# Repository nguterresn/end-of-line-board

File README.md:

## End Of Line Board for Testing

### Quick Introduction

Normally, in the world of _access control_, a [contact sensor](https://www.gensecurity.com/blog/how-do-contatct-sensors-work) is either open or closed. This is essentially true if the system does not support **end of line**.
End of line increases the number of avaialble _states_ of a contact sensor, from two to four:

| Opened | Closed | (new) Shorted | (new) Cut |
|--------|--------|---------|-----|

This is very important in Alarm and Fire systems, where these four states are essential.

### Board

This design aims to test all the possible configurations for end of line: 

|             | **Single Resistor Line Shorted** | **Single Resistor Line Cut** | **Double Resistor** |
|-------------|:--------------------------------:|:----------------------------:|:-------------------:|
| **Opened**  |                 ✅               |               ✅              |          ✅          |
| **Closed**  |                 ✅                |               ✅              |          ✅          |
| **Shorted** |                 ✅                |               ❌              |          ✅          |
| **Cut**     |                 ❌                |               ✅              |          ✅          |

There a is good [document here](https://github.com/nguterresn/end-of-line-board/blob/master/docs/EOL-Types.pdf) explaining the difference between configurations.

### 3D View

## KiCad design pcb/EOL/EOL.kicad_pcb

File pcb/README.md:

## Description
##### This is where the pcb files are. Normally, here is where a KiCad project is created. 

## Directory Structure

- **pcb**
    - bom
    - gerber
    - svg
    - ... (some package folders)

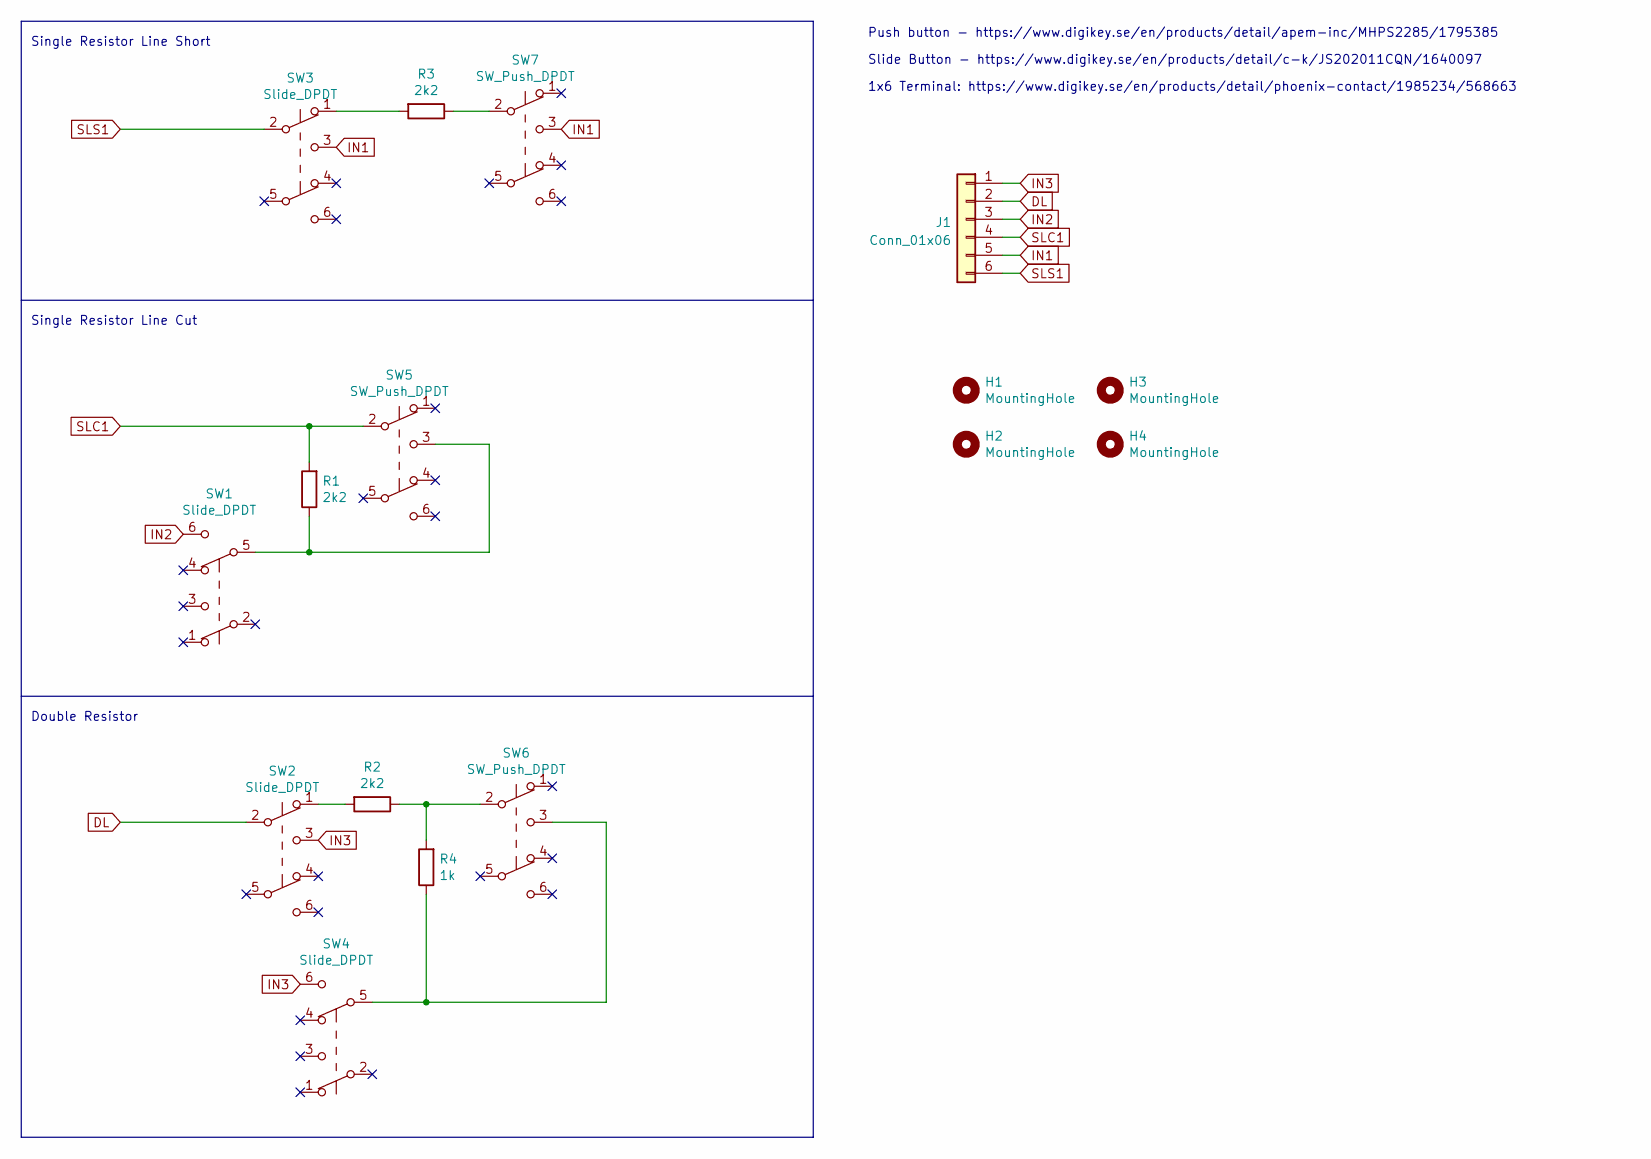
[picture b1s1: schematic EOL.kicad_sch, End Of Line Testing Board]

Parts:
H1, H2, H3, H4: MountingHole; MountingHole_3.2mm_M3_Pad_Via
J1: Conn_01x06; TerminalBlock_Phoenix_MKDS-1,5-6_1x06_P5.00mm_Horizontal; LCSC C2802619
R1, R2, R3: 2k2; R_0603_1608Metric_Pad1.05x0.95mm_HandSolder; LCSC C5140136
R4: 1k; R_0603_1608Metric_Pad1.05x0.95mm_HandSolder; LCSC C3152127
SW1, SW2, SW3, SW4: Slide_DPDT; SW_E-Switch_EG1271_DPDT; LCSC C2906278
SW5, SW6, SW7: SW_Push_DPDT; MHPS2285; LCSC C493261

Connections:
DL: J1.2, SW2.2 (B)
IN1: J1.5, SW3.3 (C), SW7.3 (C)
IN2: J1.3, SW1.6 (C)
IN3: J1.1, SW2.3 (C), SW4.6 (C)
unnamed: R1.1, SW1.5 (B), SW5.3 (C)
unnamed: R2.1, R4.2, SW6.2 (B)
unnamed: R2.2, SW2.1 (A)
unnamed: R3.1, SW7.2 (B)
unnamed: R3.2, SW3.1 (A)
unnamed: R4.1, SW4.5 (B), SW6.3 (C)
SLC1: J1.4, R1.2, SW5.2 (B)
SLS1: J1.6, SW3.2 (B)

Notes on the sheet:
1x6 Terminal: https://www.digikey.se/en/products/detail/phoenix-contact/1985234/568663
Push button - https://www.digikey.se/en/products/detail/apem-inc/MHPS2285/1795385
Single Resistor Line Cut
Slide Button - https://www.digikey.se/en/products/detail/c-k/JS202011CQN/1640097
Single Resistor Line Short
Double Resistor

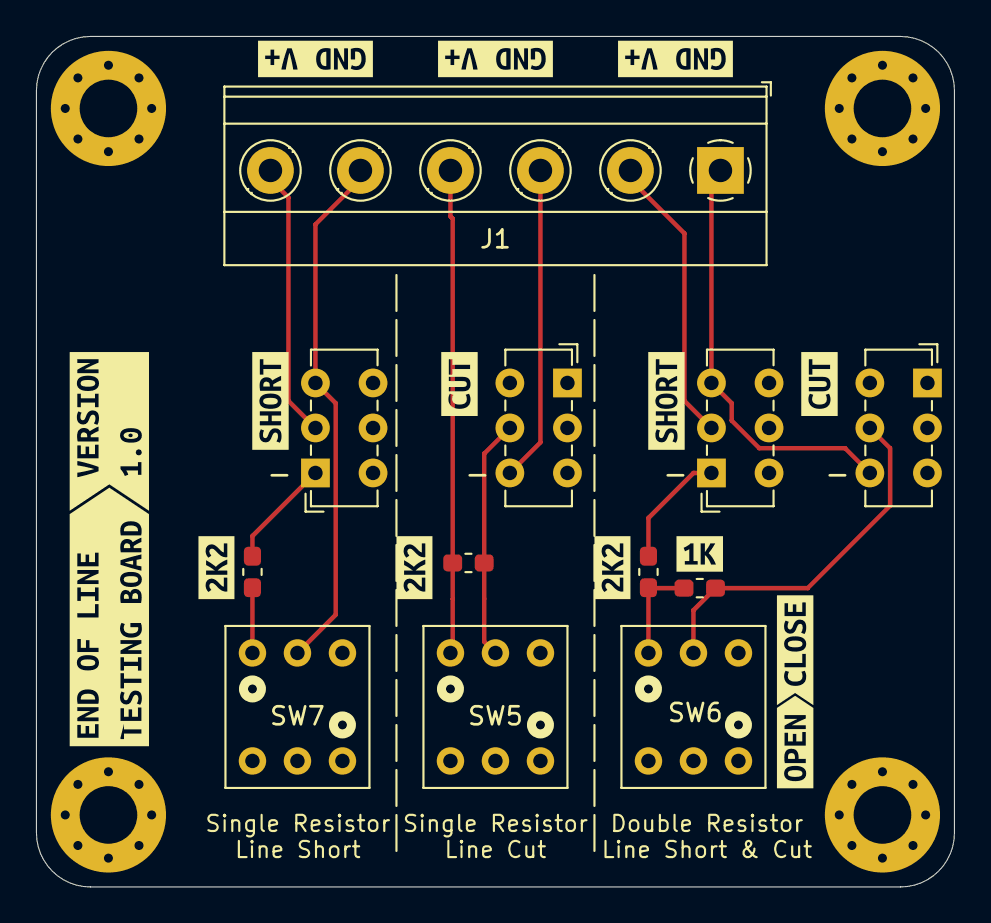
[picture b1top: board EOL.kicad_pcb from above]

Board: 2 copper layers, 51.0 x 47.2 mm, 31 parts (0 on the bottom side), 12 nets.

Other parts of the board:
kibuzzard-6481E1FA, kibuzzard-6481E1FA#2: G***; kibuzzard-6481E1FA
kibuzzard-6481E2B4: G***; kibuzzard-6481E2B4
kibuzzard-6481E2F6, kibuzzard-6481E2F6#2, kibuzzard-6481E2F6#3: G***; kibuzzard-6481E2F6
kibuzzard-6481E3F6: G***; kibuzzard-6481E3F6
kibuzzard-6481E4F7: G***; kibuzzard-6481E4F7
kibuzzard-6481E55F: G***; kibuzzard-6481E55F
kibuzzard-6481E268, kibuzzard-6481E268#2: G***; kibuzzard-6481E268
kibuzzard-6481E412: G***; kibuzzard-6481E412
kibuzzard-6482D2A7, kibuzzard-6482D2A7#2, kibuzzard-6482D2A7#3: G***; kibuzzard-6482D2A7

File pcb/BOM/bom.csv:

Comment,Designator,Footprint,LCSC
"MountingHole","H1,H2,H3,H4","MountingHole:MountingHole_3.2mm_M3_Pad_Via",""
"Conn_01x06","J1","TerminalBlock_Phoenix:TerminalBlock_Phoenix_MKDS-1,5-6_1x06_P5.00mm_Horizontal","C2802619"
"2k2","R1,R2,R3","Resistor_SMD:R_0603_1608Metric_Pad1.05x0.95mm_HandSolder","C5140136"
"1k","R4","Resistor_SMD:R_0603_1608Metric_Pad1.05x0.95mm_HandSolder","C3152127"
"Slide_DPDT","SW1,SW2,SW3,SW4","Button_Switch_THT:SW_E-Switch_EG1271_DPDT","C2906278"
"SW_Push_DPDT","SW5,SW6,SW7","External:MHPS2285","C493261"

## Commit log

2022-03-19 Removed unused files.
2022-03-19 New docs and first steps into the pcb
2022-03-19 v1.0 of the End of line board
2022-04-06 Changed from screw terminal to push terminals
2022-04-06 New 3d model, transition to kicad v6
2022-04-06 Minor changes.
2022-04-06 Update sch.
2022-04-12 New design
2022-04-17 Remove some unused files.
2022-08-13 Deleted unused files.
2023-06-08 Updated Board labels. Made them bigger 👁️
2023-06-09 Replace the terminal footprint for a screw terminal. Added the LCSC unique ids to ease the process of ordering a pcb.
2023-06-16 Added BOM , drill and gerber.
2023-06-29 box with ikea skadis support
